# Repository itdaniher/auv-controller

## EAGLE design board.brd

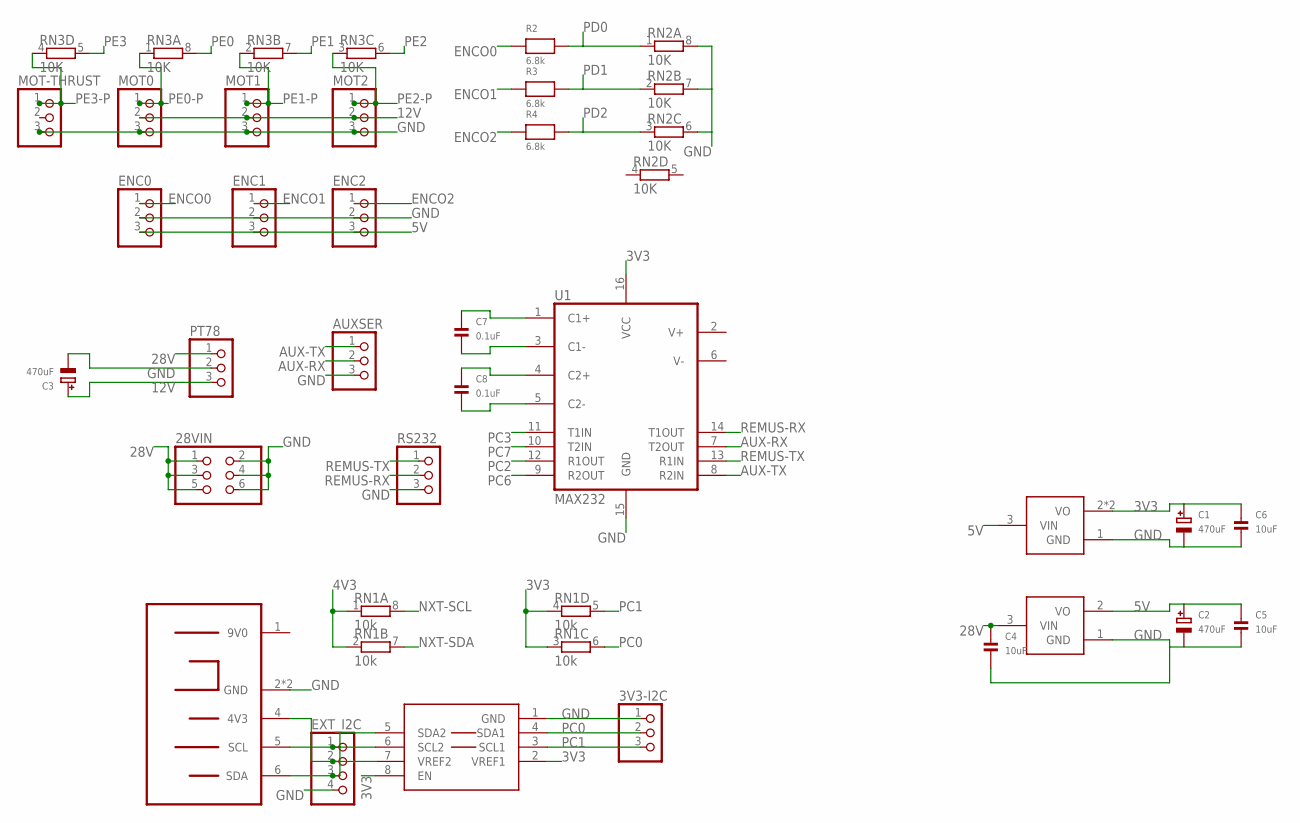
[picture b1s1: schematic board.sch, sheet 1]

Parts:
3V3-I2C: HEADER-1X3ROUND; 1X03_ROUND
28VIN: HEADER-2X3; 2X03
AUXSER: HEADER-1X3ROUND; 1X03_ROUND
C1, C2, C3: 470uF; EIA7343-31/D-W
C4, C5, C6: 10uF; 1206
C7, C8: 0.1uF; 0603
ENC0, ENC1, ENC2: HEADER-1X3ROUND; 1X03_ROUND
EXT_I2C: HEADER-1X4ROUND; 1X04_ROUND
MOT0, MOT1, MOT2: HEADER-1X3ROUND; 1X03_ROUND
MOT-THRUST: HEADER-1X3ROUND; 1X03_ROUND
PT78: HEADER-1X3ROUND; 1X03_ROUND
R2, R3, R4: 6.8k; 0603
RN1: 10k; RN8P-4R-CRA06S
RN2, RN3: 10K; RN8P-4R-CRA06S
RS232: HEADER-1X3ROUND; 1X03_ROUND
U1: MAX232; SO-16
U$1: PCA9306; SO-08
U$2: NXT-CONNECTOR; NXT-FOOTPRINT
U$3: VREGAP1117; SOT223
U$4: VREGIFX27001; TO252

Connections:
3V3: C1.+, C6.1, RN1.3 (1), RN1.4 (1), U1.16 (VCC), U$1.2 (VREF1), U$1.8 (EN), U$3.2 (VO), U$3.4 (VO); also elsewhere on the board
4V3: EXT_I2C.2, RN1.1, RN1.2 (1), U$1.7 (VREF2), U$2.4 (4V3)
5V: C2.+, C5.1, ENC0.3, ENC1.3, ENC2.3, U$3.3 (VIN), U$4.2 (VO); also elsewhere on the board
12V: C3.+, MOT0.2, MOT1.2, MOT2.2, PT78.3
28V: 28VIN.1, 28VIN.3, 28VIN.5, C4.1, PT78.1, U$4.3 (VIN)
AUX-RX: AUXSER.2, U1.7 (T2OUT)
AUX-TX: AUXSER.1, U1.8 (R2IN)
C1+: C7.1, U1.1 (C1+)
C1-: C7.2, U1.3 (C1-)
C2+: C8.1, U1.4 (C2+)
C2-: C8.2, U1.5 (C2-)
ENCO0: ENC0.1, R2.1
ENCO1: ENC1.1, R3.1
ENCO2: ENC2.1, R4.1
GND: 3V3-I2C.1, 28VIN.2, 28VIN.4, 28VIN.6, AUXSER.3, C1.-, C3.-, C4.2, C5.2, C6.2, ENC0.2, ENC1.2, ENC2.2, EXT_I2C.4, MOT0.3, MOT1.3, MOT2.3, MOT-THRUST.3, PT78.2, RN2.6 (2), RN2.7 (2), RN2.8 (2), RS232.3, U1.15 (GND), U$1.1 (GND), U$2.2 (GND), U$2.3 (GND), U$3.1 (GND), U$4.1 (GND); also elsewhere on the board
NXT-SCL: EXT_I2C.1, RN1.8 (2), U$1.6 (SCL2), U$2.5 (SCL)
NXT-SDA: EXT_I2C.3, RN1.7 (2), U$1.5 (SDA2), U$2.6 (SDA)
PC0: 3V3-I2C.2, RN1.6 (2), U$1.4 (SDA1); also elsewhere on the board
PC1: 3V3-I2C.3, RN1.5 (2), U$1.3 (SCL1); also elsewhere on the board
PC2: U1.12 (R1OUT); also elsewhere on the board
PC3: U1.11 (T1IN); also elsewhere on the board
PC6: U1.9 (R2OUT); also elsewhere on the board
PC7: U1.10 (T2IN); also elsewhere on the board
PD0: R2.2, RN2.1; also elsewhere on the board
PD1: R3.2, RN2.2 (1); also elsewhere on the board
PD2: R4.2, RN2.3 (1); also elsewhere on the board
PE0: RN3.8 (2); also elsewhere on the board
PE0-P: MOT0.1, RN3.1
PE1: RN3.7 (2); also elsewhere on the board
PE1-P: MOT1.1, RN3.2 (1)
PE2: RN3.6 (2); also elsewhere on the board
PE2-P: MOT2.1, RN3.3 (1)
PE3: RN3.5 (2); also elsewhere on the board
PE3-P: MOT-THRUST.1, RN3.4 (1)
REMUS-RX: RS232.2, U1.14 (T1OUT)
REMUS-TX: RS232.1, U1.13 (R1IN)

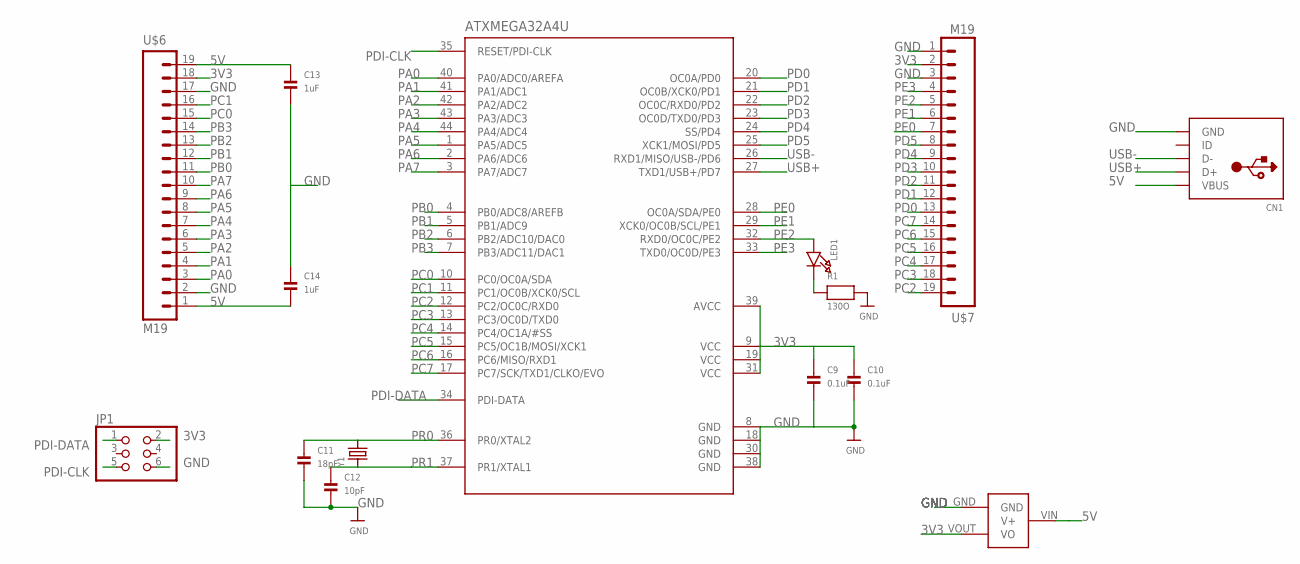
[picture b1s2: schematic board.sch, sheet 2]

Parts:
ATXMEGA32A4U: ATXMEGAXXA4U-AU; TQFP-44
C9, C10: 0.1uF; 0603
C11: 18pF; 0603
C12: 10pF; 0603
C13, C14: 1uF; 0603
CN1: USBMICROB; USB-MICROB
JP1: HEADER-2X3; 2X03
LED1: LED0603; CHIPLED_0603
R1: 130O; 0603
U$5: MCP1700; SOT23-3
U$6, U$7: M19; 1X19
Y1: CRYSTAL; NX8045GB

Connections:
3V3: ATXMEGA32A4U.9 (VCC), ATXMEGA32A4U.19 (VCC), ATXMEGA32A4U.31 (VCC), ATXMEGA32A4U.39 (AVCC), C9.1, C10.1, JP1.2, U$5.VOUT (VO), U$6.18, U$7.2; also elsewhere on the board
5V: C13.1, C14.2, CN1.P1 (VBUS), U$5.VIN (V+), U$6.1, U$6.19; also elsewhere on the board
GND: ATXMEGA32A4U.8 (GND), ATXMEGA32A4U.18 (GND), ATXMEGA32A4U.30 (GND), ATXMEGA32A4U.38 (GND), C9.2, C10.2, C11.2, C12.2, C13.2, C14.1, CN1.P5 (GND), JP1.6, R1.2, U$5.GND, U$6.2, U$6.17, U$7.1, U$7.3; also elsewhere on the board
unnamed: LED1.C, R1.1
PA0: ATXMEGA32A4U.40 (PA0/ADC0/AREFA), U$6.3
PA1: ATXMEGA32A4U.41 (PA1/ADC1), U$6.4
PA2: ATXMEGA32A4U.42 (PA2/ADC2), U$6.5
PA3: ATXMEGA32A4U.43 (PA3/ADC3), U$6.6
PA4: ATXMEGA32A4U.44 (PA4/ADC4), U$6.7
PA5: ATXMEGA32A4U.1 (PA5/ADC5), U$6.8
PA6: ATXMEGA32A4U.2 (PA6/ADC6), U$6.9
PA7: ATXMEGA32A4U.3 (PA7/ADC7), U$6.10
PB0: ATXMEGA32A4U.4 (PB0/ADC8/AREFB), U$6.11
PB1: ATXMEGA32A4U.5 (PB1/ADC9), U$6.12
PB2: ATXMEGA32A4U.6 (PB2/ADC10/DAC0), U$6.13
PB3: ATXMEGA32A4U.7 (PB3/ADC11/DAC1), U$6.14
PC0: ATXMEGA32A4U.10 (PC0/OC0A/SDA), U$6.15; also elsewhere on the board
PC1: ATXMEGA32A4U.11 (PC1/OC0B/XCK0/SCL), U$6.16; also elsewhere on the board
PC2: ATXMEGA32A4U.12 (PC2/OC0C/RXD0), U$7.19; also elsewhere on the board
PC3: ATXMEGA32A4U.13 (PC3/OC0D/TXD0), U$7.18; also elsewhere on the board
PC4: ATXMEGA32A4U.14 (PC4/OC1A/#SS), U$7.17
PC5: ATXMEGA32A4U.15 (PC5/OC1B/MOSI/XCK1), U$7.16
PC6: ATXMEGA32A4U.16 (PC6/MISO/RXD1), U$7.15; also elsewhere on the board
PC7: ATXMEGA32A4U.17 (PC7/SCK/TXD1/CLKO/EVO), U$7.14; also elsewhere on the board
PD0: ATXMEGA32A4U.20 (OC0A/PD0), U$7.13; also elsewhere on the board
PD1: ATXMEGA32A4U.21 (OC0B/XCK0/PD1), U$7.12; also elsewhere on the board
PD2: ATXMEGA32A4U.22 (OC0C/RXD0/PD2), U$7.11; also elsewhere on the board
PD3: ATXMEGA32A4U.23 (OC0D/TXD0/PD3), U$7.10
PD4: ATXMEGA32A4U.24 (SS/PD4), U$7.9
PD5: ATXMEGA32A4U.25 (XCK1/MOSI/PD5), U$7.8
PDI-CLK: ATXMEGA32A4U.35 (RESET/PDI-CLK), JP1.5
PDI-DATA: ATXMEGA32A4U.34 (PDI-DATA), JP1.1
PE0: ATXMEGA32A4U.28 (OC0A/SDA/PE0), U$7.7; also elsewhere on the board
PE1: ATXMEGA32A4U.29 (XCK0/OC0B/SCL/PE1), U$7.6; also elsewhere on the board
PE2: ATXMEGA32A4U.32 (RXD0/OC0C/PE2), LED1.A, U$7.5; also elsewhere on the board
PE3: ATXMEGA32A4U.33 (TXD0/OC0D/PE3), U$7.4; also elsewhere on the board
PR0: ATXMEGA32A4U.36 (PR0/XTAL2), C11.1, Y1.P$2 (2)
PR1: ATXMEGA32A4U.37 (PR1/XTAL1), C12.1, Y1.P$1 (1)
USB+: ATXMEGA32A4U.27 (TXD1/USB+/PD7), CN1.P3 (D+)
USB-: ATXMEGA32A4U.26 (RXD1/MISO/USB-/PD6), CN1.P2 (D-)

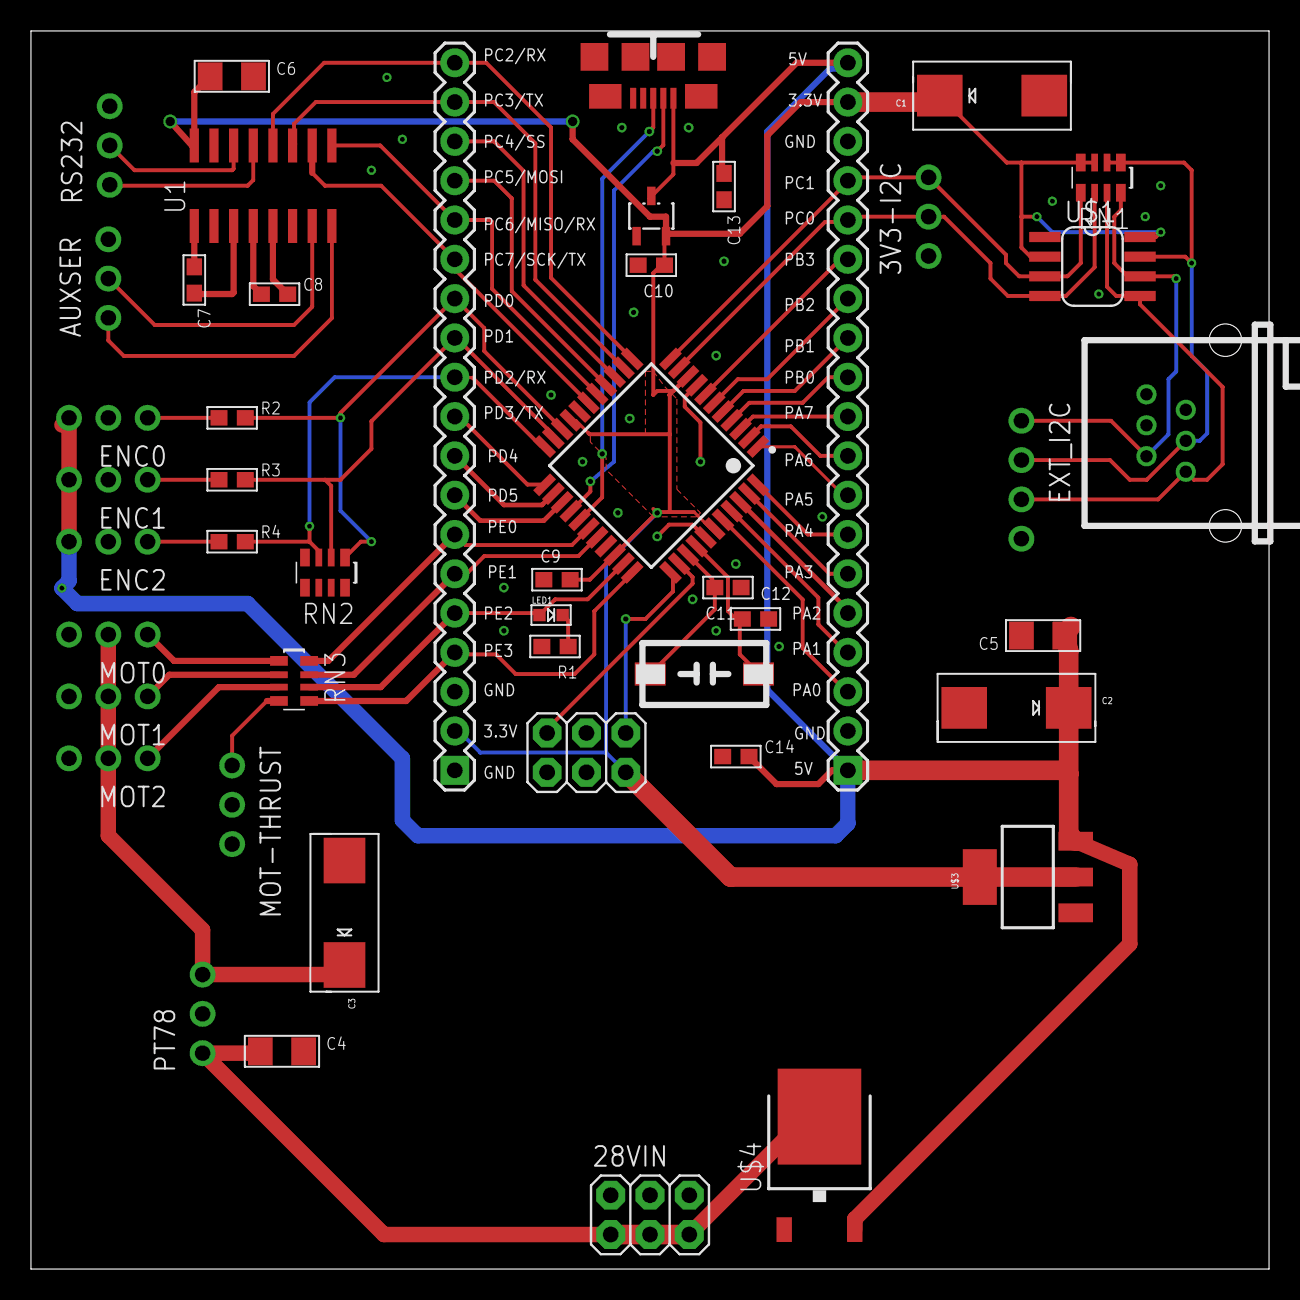
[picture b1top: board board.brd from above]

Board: 2 copper layers, 80.0 x 80.0 mm, 47 parts (0 on the bottom side), 60 nets.

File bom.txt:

28VIN                       2X03
3V3-I2C                     1X03
AUXSER                      1X03
REMUS-SER                   1X03
USB-MICROB

PT78                        1X03

C1           470uF          EIA7343
C2           470uF          EIA7343
C3           470uF          EIA7343-
C4           10uF           1206
C5           10uF           1206
C6           10uF           1206
C7           0.1uF          0603
C8           0.1uF          0603
C9           0.1uF          0603
C10          0.1uF          0603 
C11          18pF           0603
C12          10pF           0603
C13          1uF            0603
C14          1uF            0603
R1           130o           0603
R2           6.8k           0603
R3           6.8k           0603
R4           6.8k           0603
RN1          10k            RN8P-4R-CRA06S
RN2          10k            RN8P-4R-CRA06S
RN3          10k            RN8P-4R-CRA06S
LED1                        0603


PCA9306      SO-08
NXT          NXT-FOOTPRINT
AP1117       SOT223
IFX27001     TO252
MCP1700      SOT23-3
SN75C3232    SO-16
ATXMEGA32A4U TQFP-44

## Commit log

2012-11-26 initial commit w/ braindump
2012-11-26 added links to interface circuitry
2012-11-26 added base board as a git submodule
2012-11-26 added link to purchased NXT interface connectors
2012-11-26 added link to PCA9306, sucklesser I2C level shifter
2012-11-26 added bits of BOM
2012-11-28 few thoughts on powering etc
2012-11-28 add P/N for power wing
2012-11-29 notes on motor psu solutions
2012-11-29 link to boost regulator datasheet
2012-12-01 added NXT connector from Silas. A++
2012-12-01 added TODO list
2012-12-01 crossing some stuff off the list!
2012-12-01 updated 12v/3v3 interface chip selection
2012-12-01 add mechanical constraints
2012-12-02 done
2012-12-02 added prelim schem
2012-12-02 removed slightly incorrect nxt drawing in favor of correct file in EAGLE
2012-12-20 added board files
2012-12-20 added relevant writeups
2012-12-20 added copies of datasheets - NB to purists: sorry for binary blobs in version control...
2012-12-20 added mechanical redesign documentation
2012-12-20 rename board files to be sane
2012-12-20 add p/n for d-sub conn
2012-12-20 housecleaning
2012-12-20 added gitignore, tweaked board
2012-12-20 add some part values, nudge some traces
2012-12-27 added BOM info

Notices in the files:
board.brd:
CC-By-SA
